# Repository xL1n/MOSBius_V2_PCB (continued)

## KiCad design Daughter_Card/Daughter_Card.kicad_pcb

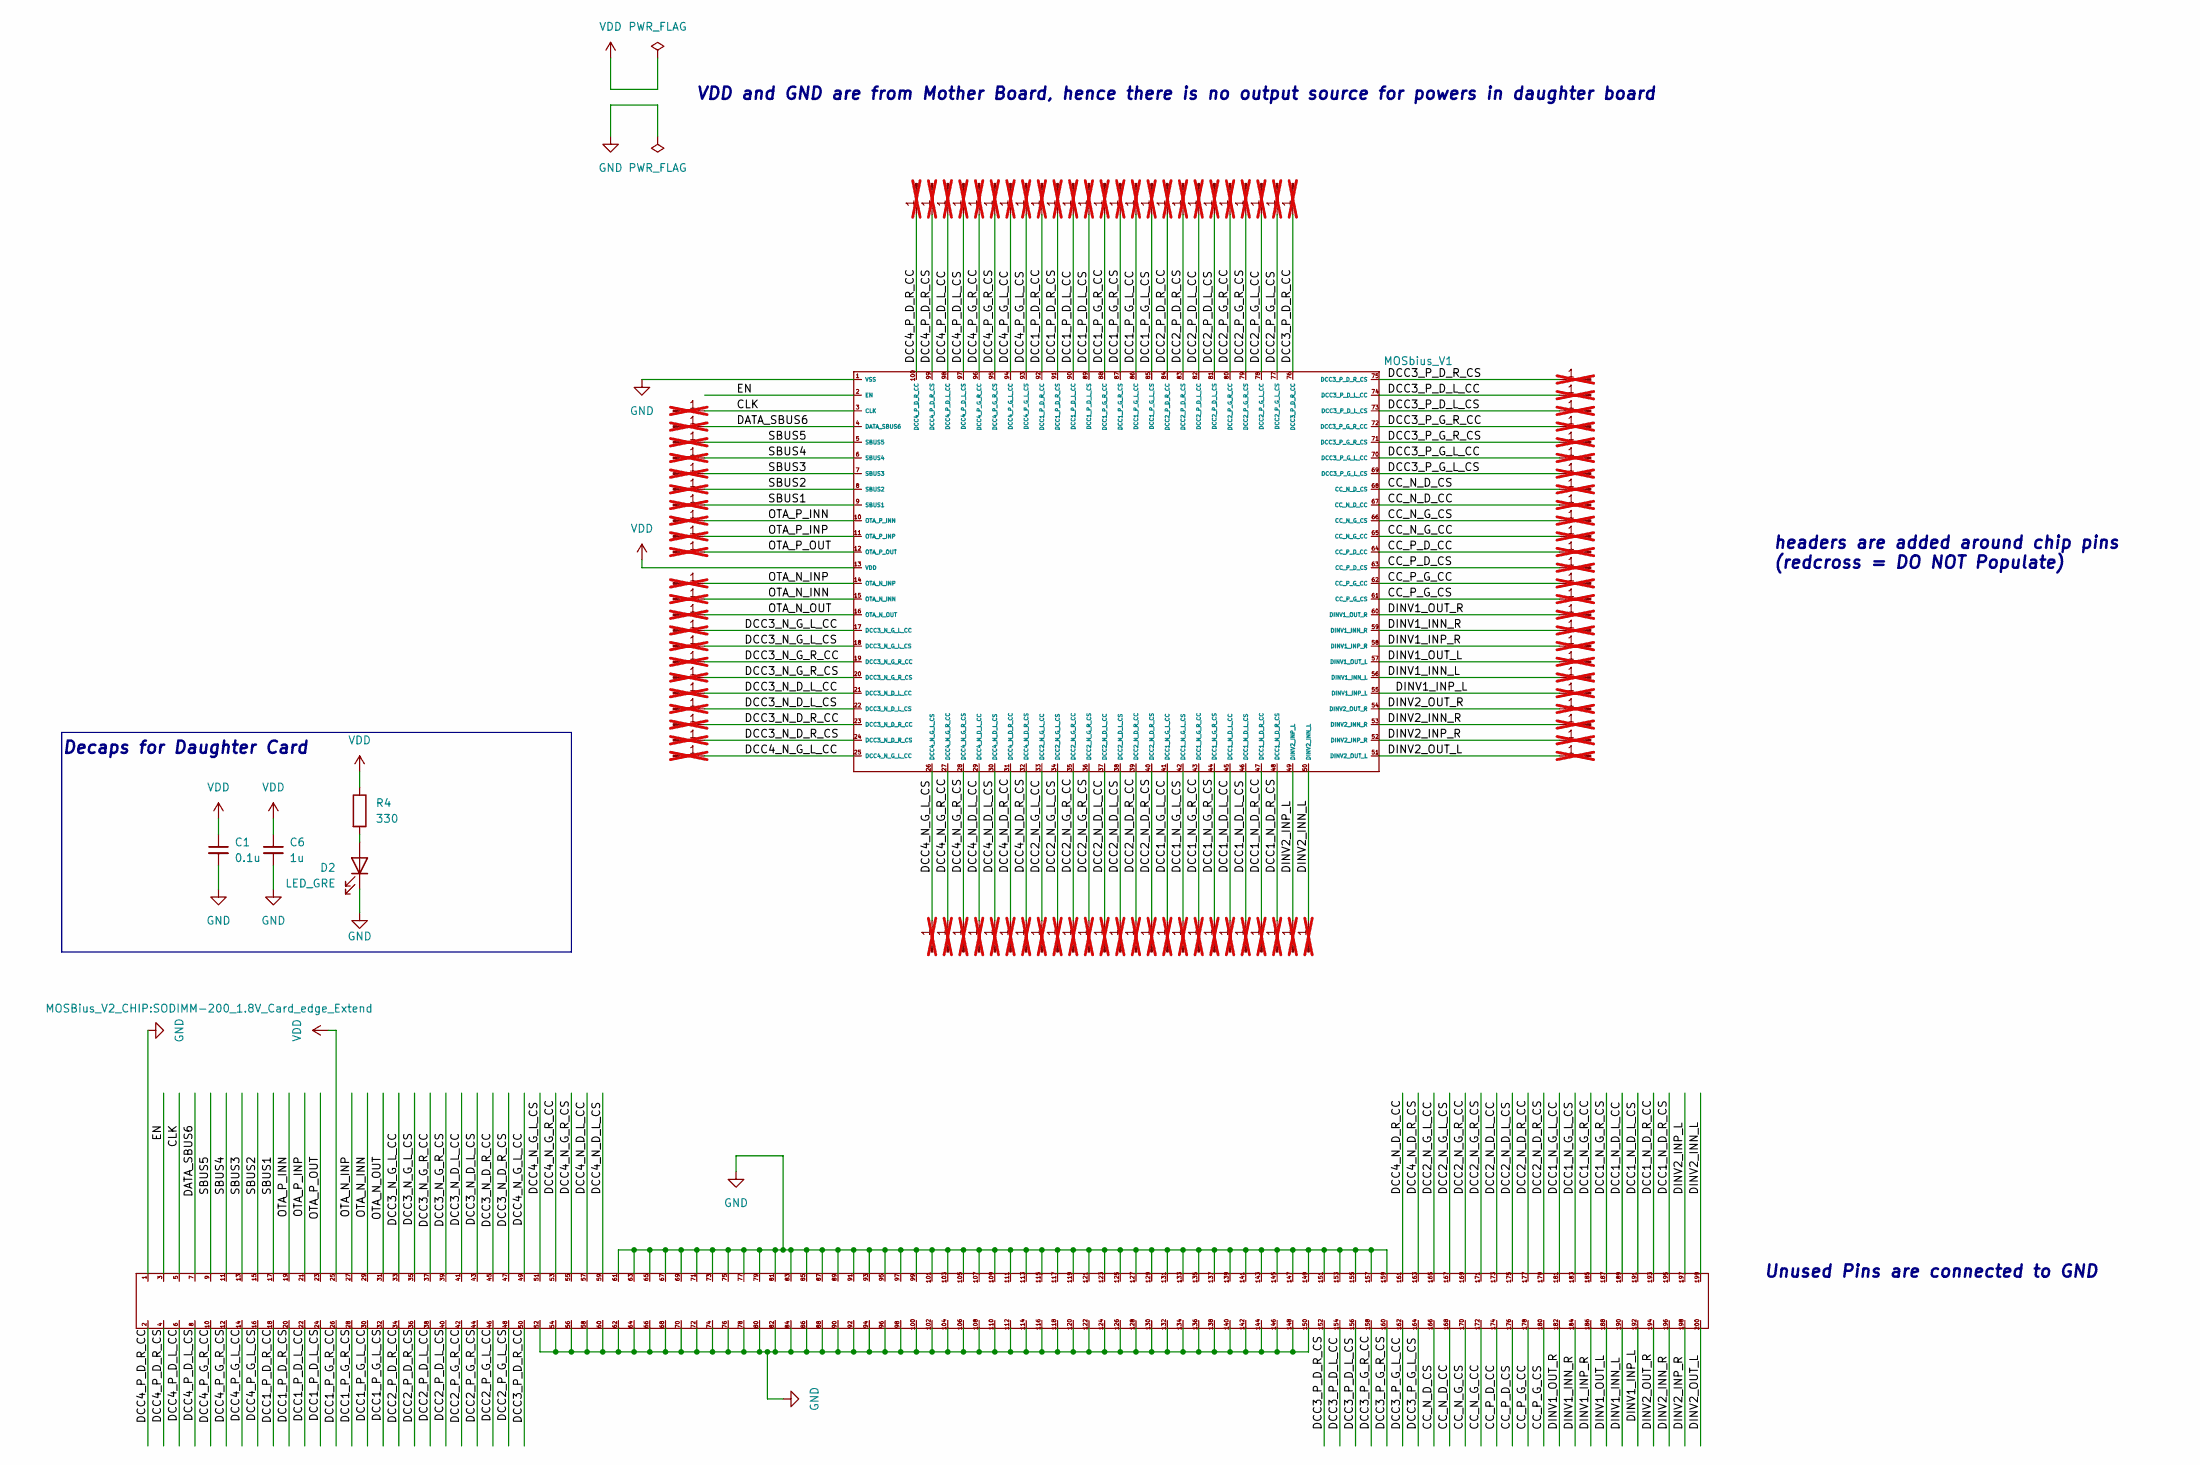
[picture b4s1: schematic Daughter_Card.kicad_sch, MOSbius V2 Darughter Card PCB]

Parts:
C1: 0.1u; C_0603_1608Metric
C6: 1u; C_0603_1608Metric
D2: LED_GRE; LED_150120RS75000_WRE
Daughter_Card_PIN1: SODIMM-200_1.8V_Card_edge_Extend
MOSbius_V1: MOSbius_V2; ArtInChip_QFN-100-1EP_12x12mm_P0.4mm_EP7.4x7.4mm
P3, P4, P5, P6, P7, P8, P9, P10, P11, P12, P14, P15, P16, P17, P18, P19, P20, P21, P22, P23, P24, P25, P26, P27, P28, P29, P30, P31, P32, P33, P34, P35, P36, P37, P38, P39, P40, P41, P42, P43, P44, P45, P46, P47, P48, P49, P50, P51, P52, P53, P54, P55, P56, P57, P58, P59, P60, P61, P62, P63, P64, P65, P66, P67, P68, P69, P70, P71, P72, P73, P74, P75, P76, P77, P78, P79, P80, P81, P82, P83, P84, P85, P86, P87, P88, P89, P90, P91, P92, P93, P94, P95, P96, P97, P98, P99, P100: Conn_01x01_Pin; PinHeader_1x01_P1.00mm_Vertical; not fitted
R4: 330; R_0603_1608Metric

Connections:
/CC_N_D_CC: Daughter_Card_PIN1.168, MOSbius_V1.67 (CC_N_D_CC), P67.1; also elsewhere on the board
/CC_N_D_CS: Daughter_Card_PIN1.166, MOSbius_V1.68 (CC_N_D_CS), P68.1; also elsewhere on the board
/CC_N_G_CC: Daughter_Card_PIN1.172, MOSbius_V1.65 (CC_N_G_CC), P65.1; also elsewhere on the board
/CC_N_G_CS: Daughter_Card_PIN1.170, MOSbius_V1.66 (CC_N_G_CS), P66.1; also elsewhere on the board
/CC_P_D_CC: Daughter_Card_PIN1.174, MOSbius_V1.64 (CC_P_D_CC), P64.1; also elsewhere on the board
/CC_P_D_CS: Daughter_Card_PIN1.176, MOSbius_V1.63 (CC_P_D_CS), P63.1; also elsewhere on the board
/CC_P_G_CC: Daughter_Card_PIN1.178, MOSbius_V1.62 (CC_P_G_CC), P62.1; also elsewhere on the board
/CC_P_G_CS: Daughter_Card_PIN1.180, MOSbius_V1.61 (CC_P_G_CS), P61.1; also elsewhere on the board
/CLK: Daughter_Card_PIN1.5, MOSbius_V1.3 (CLK), P3.1; also elsewhere on the board
/DATA_SBUS6: Daughter_Card_PIN1.7, MOSbius_V1.4 (DATA_SBUS6), P4.1; also elsewhere on the board
/DCC1_N_D_L_CC: Daughter_Card_PIN1.189, MOSbius_V1.45 (DCC1_N_D_L_CC), P45.1; also elsewhere on the board
/DCC1_N_D_L_CS: Daughter_Card_PIN1.191, MOSbius_V1.46 (DCC1_N_D_L_CS), P46.1; also elsewhere on the board
/DCC1_N_D_R_CC: Daughter_Card_PIN1.193, MOSbius_V1.47 (DCC1_N_D_R_CC), P47.1; also elsewhere on the board
/DCC1_N_D_R_CS: Daughter_Card_PIN1.195, MOSbius_V1.48 (DCC1_N_D_R_CS), P48.1; also elsewhere on the board
/DCC1_N_G_L_CC: Daughter_Card_PIN1.181, MOSbius_V1.41 (DCC1_N_G_L_CC), P41.1; also elsewhere on the board
/DCC1_N_G_L_CS: Daughter_Card_PIN1.183, MOSbius_V1.42 (DCC1_N_G_L_CS), P42.1; also elsewhere on the board
/DCC1_N_G_R_CC: Daughter_Card_PIN1.185, MOSbius_V1.43 (DCC1_N_G_R_CC), P43.1; also elsewhere on the board
/DCC1_N_G_R_CS: Daughter_Card_PIN1.187, MOSbius_V1.44 (DCC1_N_G_R_CS), P44.1; also elsewhere on the board
/DCC1_P_D_L_CC: Daughter_Card_PIN1.22, MOSbius_V1.90 (DCC1_P_D_L_CC), P90.1; also elsewhere on the board
/DCC1_P_D_L_CS: Daughter_Card_PIN1.24, MOSbius_V1.89 (DCC1_P_D_L_CS), P89.1; also elsewhere on the board
/DCC1_P_D_R_CC: Daughter_Card_PIN1.18, MOSbius_V1.92 (DCC1_P_D_R_CC), P92.1; also elsewhere on the board
/DCC1_P_D_R_CS: Daughter_Card_PIN1.20, MOSbius_V1.91 (DCC1_P_D_R_CS), P91.1; also elsewhere on the board
/DCC1_P_G_L_CC: Daughter_Card_PIN1.30, MOSbius_V1.86 (DCC1_P_G_L_CC), P86.1; also elsewhere on the board
/DCC1_P_G_L_CS: Daughter_Card_PIN1.32, MOSbius_V1.85 (DCC1_P_G_L_CS), P85.1; also elsewhere on the board
/DCC1_P_G_R_CC: Daughter_Card_PIN1.26, MOSbius_V1.88 (DCC1_P_G_R_CC), P88.1; also elsewhere on the board
/DCC1_P_G_R_CS: Daughter_Card_PIN1.28, MOSbius_V1.87 (DCC1_P_G_R_CS), P87.1; also elsewhere on the board
/DCC2_N_D_L_CC: Daughter_Card_PIN1.173, MOSbius_V1.37 (DCC2_N_D_L_CC), P37.1; also elsewhere on the board
/DCC2_N_D_L_CS: Daughter_Card_PIN1.175, MOSbius_V1.38 (DCC2_N_D_L_CS), P38.1; also elsewhere on the board
/DCC2_N_D_R_CC: Daughter_Card_PIN1.177, MOSbius_V1.39 (DCC2_N_D_R_CC), P39.1; also elsewhere on the board
/DCC2_N_D_R_CS: Daughter_Card_PIN1.179, MOSbius_V1.40 (DCC2_N_D_R_CS), P40.1; also elsewhere on the board
/DCC2_N_G_L_CC: Daughter_Card_PIN1.165, MOSbius_V1.33 (DCC2_N_G_L_CC), P33.1; also elsewhere on the board
/DCC2_N_G_L_CS: Daughter_Card_PIN1.167, MOSbius_V1.34 (DCC2_N_G_L_CS), P34.1; also elsewhere on the board
/DCC2_N_G_R_CC: Daughter_Card_PIN1.169, MOSbius_V1.35 (DCC2_N_G_R_CC), P35.1; also elsewhere on the board
/DCC2_N_G_R_CS: Daughter_Card_PIN1.171, MOSbius_V1.36 (DCC2_N_G_R_CS), P36.1; also elsewhere on the board
/DCC2_P_D_L_CC: Daughter_Card_PIN1.38, MOSbius_V1.82 (DCC2_P_D_L_CC), P82.1; also elsewhere on the board
/DCC2_P_D_L_CS: Daughter_Card_PIN1.40, MOSbius_V1.81 (DCC2_P_D_L_CS), P81.1; also elsewhere on the board
/DCC2_P_D_R_CC: Daughter_Card_PIN1.34, MOSbius_V1.84 (DCC2_P_D_R_CC), P84.1; also elsewhere on the board
/DCC2_P_D_R_CS: Daughter_Card_PIN1.36, MOSbius_V1.83 (DCC2_P_D_R_CS), P83.1; also elsewhere on the board
/DCC2_P_G_L_CC: Daughter_Card_PIN1.46, MOSbius_V1.78 (DCC2_P_G_L_CC), P78.1; also elsewhere on the board
/DCC2_P_G_L_CS: Daughter_Card_PIN1.48, MOSbius_V1.77 (DCC2_P_G_L_CS), P77.1; also elsewhere on the board
/DCC2_P_G_R_CC: Daughter_Card_PIN1.42, MOSbius_V1.80 (DCC2_P_G_R_CC), P80.1; also elsewhere on the board
/DCC2_P_G_R_CS: Daughter_Card_PIN1.44, MOSbius_V1.79 (DCC2_P_G_R_CS), P79.1; also elsewhere on the board
/DCC3_N_D_L_CC: Daughter_Card_PIN1.41, MOSbius_V1.21 (DCC3_N_D_L_CC), P21.1; also elsewhere on the board
/DCC3_N_D_L_CS: Daughter_Card_PIN1.43, MOSbius_V1.22 (DCC3_N_D_L_CS), P22.1; also elsewhere on the board
/DCC3_N_D_R_CC: Daughter_Card_PIN1.45, MOSbius_V1.23 (DCC3_N_D_R_CC), P23.1; also elsewhere on the board
/DCC3_N_D_R_CS: Daughter_Card_PIN1.47, MOSbius_V1.24 (DCC3_N_D_R_CS), P24.1; also elsewhere on the board
/DCC3_N_G_L_CC: Daughter_Card_PIN1.33, MOSbius_V1.17 (DCC3_N_G_L_CC), P17.1; also elsewhere on the board
/DCC3_N_G_L_CS: Daughter_Card_PIN1.35, MOSbius_V1.18 (DCC3_N_G_L_CS), P18.1; also elsewhere on the board
/DCC3_N_G_R_CC: Daughter_Card_PIN1.37, MOSbius_V1.19 (DCC3_N_G_R_CC), P19.1; also elsewhere on the board
/DCC3_N_G_R_CS: Daughter_Card_PIN1.39, MOSbius_V1.20 (DCC3_N_G_R_CS), P20.1; also elsewhere on the board
/DCC3_P_D_L_CC: Daughter_Card_PIN1.154, MOSbius_V1.74 (DCC3_P_D_L_CC), P74.1; also elsewhere on the board
/DCC3_P_D_L_CS: Daughter_Card_PIN1.156, MOSbius_V1.73 (DCC3_P_D_L_CS), P73.1; also elsewhere on the board
/DCC3_P_D_R_CC: Daughter_Card_PIN1.50, MOSbius_V1.76 (DCC3_P_D_R_CC), P76.1; also elsewhere on the board
/DCC3_P_D_R_CS: Daughter_Card_PIN1.152, MOSbius_V1.75 (DCC3_P_D_R_CS), P75.1; also elsewhere on the board
/DCC3_P_G_L_CC: Daughter_Card_PIN1.162, MOSbius_V1.70 (DCC3_P_G_L_CC), P70.1; also elsewhere on the board
/DCC3_P_G_L_CS: Daughter_Card_PIN1.164, MOSbius_V1.69 (DCC3_P_G_L_CS), P69.1; also elsewhere on the board
/DCC3_P_G_R_CC: Daughter_Card_PIN1.158, MOSbius_V1.72 (DCC3_P_G_R_CC), P72.1; also elsewhere on the board
/DCC3_P_G_R_CS: Daughter_Card_PIN1.160, MOSbius_V1.71 (DCC3_P_G_R_CS), P71.1; also elsewhere on the board
/DCC4_N_D_L_CC: Daughter_Card_PIN1.57, MOSbius_V1.29 (DCC4_N_D_L_CC), P29.1; also elsewhere on the board
/DCC4_N_D_L_CS: Daughter_Card_PIN1.59, MOSbius_V1.30 (DCC4_N_D_L_CS), P30.1; also elsewhere on the board
/DCC4_N_D_R_CC: Daughter_Card_PIN1.161, MOSbius_V1.31 (DCC4_N_D_R_CC), P31.1; also elsewhere on the board
/DCC4_N_D_R_CS: Daughter_Card_PIN1.163, MOSbius_V1.32 (DCC4_N_D_R_CS), P32.1; also elsewhere on the board
/DCC4_N_G_L_CC: Daughter_Card_PIN1.49, MOSbius_V1.25 (DCC4_N_G_L_CC), P25.1; also elsewhere on the board
/DCC4_N_G_L_CS: Daughter_Card_PIN1.51, MOSbius_V1.26 (DCC4_N_G_L_CS), P26.1; also elsewhere on the board
/DCC4_N_G_R_CC: Daughter_Card_PIN1.53, MOSbius_V1.27 (DCC4_N_G_R_CC), P27.1; also elsewhere on the board
/DCC4_N_G_R_CS: Daughter_Card_PIN1.55, MOSbius_V1.28 (DCC4_N_G_R_CS), P28.1; also elsewhere on the board
/DCC4_P_D_L_CC: Daughter_Card_PIN1.6, MOSbius_V1.98 (DCC4_P_D_L_CC), P98.1; also elsewhere on the board
/DCC4_P_D_L_CS: Daughter_Card_PIN1.8, MOSbius_V1.97 (DCC4_P_D_L_CS), P97.1; also elsewhere on the board
/DCC4_P_D_R_CC: Daughter_Card_PIN1.2, MOSbius_V1.100 (DCC4_P_D_R_CC), P100.1; also elsewhere on the board
/DCC4_P_D_R_CS: Daughter_Card_PIN1.4, MOSbius_V1.99 (DCC4_P_D_R_CS), P99.1; also elsewhere on the board
/DCC4_P_G_L_CC: Daughter_Card_PIN1.14, MOSbius_V1.94 (DCC4_P_G_L_CC), P94.1; also elsewhere on the board
/DCC4_P_G_L_CS: Daughter_Card_PIN1.16, MOSbius_V1.93 (DCC4_P_G_L_CS), P93.1; also elsewhere on the board
/DCC4_P_G_R_CC: Daughter_Card_PIN1.10, MOSbius_V1.96 (DCC4_P_G_R_CC), P96.1; also elsewhere on the board
/DCC4_P_G_R_CS: Daughter_Card_PIN1.12, MOSbius_V1.95 (DCC4_P_G_R_CS), P95.1; also elsewhere on the board
/DINV1_INN_L: Daughter_Card_PIN1.190, MOSbius_V1.56 (DINV1_INN_L), P56.1; also elsewhere on the board
/DINV1_INN_R: Daughter_Card_PIN1.184, MOSbius_V1.59 (DINV1_INN_R), P59.1; also elsewhere on the board
/DINV1_INP_L: Daughter_Card_PIN1.192, MOSbius_V1.55 (DINV1_INP_L), P55.1; also elsewhere on the board
/DINV1_INP_R: Daughter_Card_PIN1.186, MOSbius_V1.58 (DINV1_INP_R), P58.1; also elsewhere on the board
/DINV1_OUT_L: Daughter_Card_PIN1.188, MOSbius_V1.57 (DINV1_OUT_L), P57.1; also elsewhere on the board
/DINV1_OUT_R: Daughter_Card_PIN1.182, MOSbius_V1.60 (DINV1_OUT_R), P60.1; also elsewhere on the board
/DINV2_INN_L: Daughter_Card_PIN1.199, MOSbius_V1.50 (DINV2_INN_L), P50.1; also elsewhere on the board
/DINV2_INN_R: Daughter_Card_PIN1.196, MOSbius_V1.53 (DINV2_INN_R), P53.1; also elsewhere on the board
/DINV2_INP_L: Daughter_Card_PIN1.197, MOSbius_V1.49 (DINV2_INP_L), P49.1; also elsewhere on the board
/DINV2_INP_R: Daughter_Card_PIN1.198, MOSbius_V1.52 (DINV2_INP_R), P52.1; also elsewhere on the board
/DINV2_OUT_L: Daughter_Card_PIN1.200, MOSbius_V1.51 (DINV2_OUT_L), P51.1; also elsewhere on the board
/DINV2_OUT_R: Daughter_Card_PIN1.194, MOSbius_V1.54 (DINV2_OUT_R), P54.1; also elsewhere on the board
/EN: Daughter_Card_PIN1.3, MOSbius_V1.2 (EN); also elsewhere on the board
/OTA_N_INN: Daughter_Card_PIN1.29, MOSbius_V1.15 (OTA_N_INN), P15.1; also elsewhere on the board
/OTA_N_INP: Daughter_Card_PIN1.27, MOSbius_V1.14 (OTA_N_INP), P14.1; also elsewhere on the board
/OTA_N_OUT: Daughter_Card_PIN1.31, MOSbius_V1.16 (OTA_N_OUT), P16.1; also elsewhere on the board
/OTA_P_INN: Daughter_Card_PIN1.19, MOSbius_V1.10 (OTA_P_INN), P10.1; also elsewhere on the board
/OTA_P_INP: Daughter_Card_PIN1.21, MOSbius_V1.11 (OTA_P_INP), P11.1; also elsewhere on the board
/OTA_P_OUT: Daughter_Card_PIN1.23, MOSbius_V1.12 (OTA_P_OUT), P12.1; also elsewhere on the board
/SBUS1: Daughter_Card_PIN1.17, MOSbius_V1.9 (SBUS1), P9.1; also elsewhere on the board
/SBUS2: Daughter_Card_PIN1.15, MOSbius_V1.8 (SBUS2), P8.1; also elsewhere on the board
/SBUS3: Daughter_Card_PIN1.13, MOSbius_V1.7 (SBUS3), P7.1; also elsewhere on the board
/SBUS4: Daughter_Card_PIN1.11, MOSbius_V1.6 (SBUS4), P6.1; also elsewhere on the board
/SBUS5: Daughter_Card_PIN1.9, MOSbius_V1.5 (SBUS5), P5.1; also elsewhere on the board
GND: C1.2, C6.2, D2.1 (K), Daughter_Card_PIN1.1, Daughter_Card_PIN1.52, Daughter_Card_PIN1.54, Daughter_Card_PIN1.56, Daughter_Card_PIN1.58, Daughter_Card_PIN1.60, Daughter_Card_PIN1.61, Daughter_Card_PIN1.62, Daughter_Card_PIN1.63, Daughter_Card_PIN1.64, Daughter_Card_PIN1.65, Daughter_Card_PIN1.66, Daughter_Card_PIN1.67, Daughter_Card_PIN1.68, Daughter_Card_PIN1.69, Daughter_Card_PIN1.70, Daughter_Card_PIN1.71, Daughter_Card_PIN1.72, Daughter_Card_PIN1.73, Daughter_Card_PIN1.74, Daughter_Card_PIN1.75, Daughter_Card_PIN1.76, Daughter_Card_PIN1.77, Daughter_Card_PIN1.78, Daughter_Card_PIN1.79, Daughter_Card_PIN1.80, Daughter_Card_PIN1.81, Daughter_Card_PIN1.82, Daughter_Card_PIN1.83, Daughter_Card_PIN1.84, Daughter_Card_PIN1.85, Daughter_Card_PIN1.86, Daughter_Card_PIN1.87, Daughter_Card_PIN1.88, Daughter_Card_PIN1.89, Daughter_Card_PIN1.90, Daughter_Card_PIN1.91, Daughter_Card_PIN1.92, Daughter_Card_PIN1.93, Daughter_Card_PIN1.94, Daughter_Card_PIN1.95, Daughter_Card_PIN1.96, Daughter_Card_PIN1.97, Daughter_Card_PIN1.98, Daughter_Card_PIN1.99, Daughter_Card_PIN1.100, Daughter_Card_PIN1.101, Daughter_Card_PIN1.102, Daughter_Card_PIN1.103, Daughter_Card_PIN1.104, Daughter_Card_PIN1.105, Daughter_Card_PIN1.106, Daughter_Card_PIN1.107, Daughter_Card_PIN1.108, Daughter_Card_PIN1.109, Daughter_Card_PIN1.110, Daughter_Card_PIN1.111, Daughter_Card_PIN1.112, Daughter_Card_PIN1.113, Daughter_Card_PIN1.114, Daughter_Card_PIN1.115, Daughter_Card_PIN1.116, Daughter_Card_PIN1.117, Daughter_Card_PIN1.118, Daughter_Card_PIN1.119, Daughter_Card_PIN1.120, Daughter_Card_PIN1.121, Daughter_Card_PIN1.122, Daughter_Card_PIN1.123, Daughter_Card_PIN1.124, Daughter_Card_PIN1.125, Daughter_Card_PIN1.126, Daughter_Card_PIN1.127, Daughter_Card_PIN1.128, Daughter_Card_PIN1.129, Daughter_Card_PIN1.130, Daughter_Card_PIN1.131, Daughter_Card_PIN1.132, Daughter_Card_PIN1.133, Daughter_Card_PIN1.134, Daughter_Card_PIN1.135, Daughter_Card_PIN1.136, Daughter_Card_PIN1.137, Daughter_Card_PIN1.138, Daughter_Card_PIN1.139, Daughter_Card_PIN1.140, Daughter_Card_PIN1.141, Daughter_Card_PIN1.142, Daughter_Card_PIN1.143, Daughter_Card_PIN1.144, Daughter_Card_PIN1.145, Daughter_Card_PIN1.146, Daughter_Card_PIN1.147, Daughter_Card_PIN1.148, Daughter_Card_PIN1.149, Daughter_Card_PIN1.150, Daughter_Card_PIN1.151, Daughter_Card_PIN1.153, Daughter_Card_PIN1.155, Daughter_Card_PIN1.157, Daughter_Card_PIN1.159, MOSbius_V1.1 (VSS); also elsewhere on the board
unnamed: D2.2 (A), R4.2
VDD: C1.1, C6.1, Daughter_Card_PIN1.25, MOSbius_V1.13 (VDD), R4.1; also elsewhere on the board

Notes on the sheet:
headers are added around chip pins (redcross = DO NOT Populate)
Decaps for Daughter Card
Unused Pins are connected to GND
VDD and GND are from Mother Board, hence there is no output source for powers in daughter board

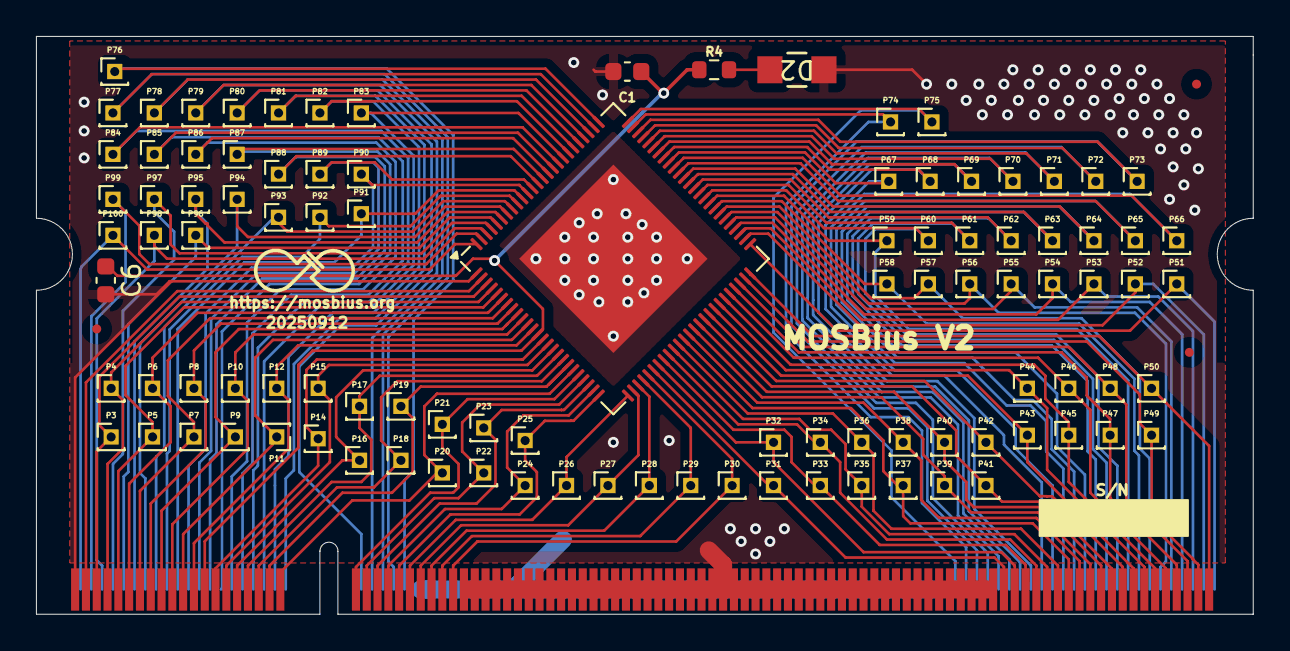
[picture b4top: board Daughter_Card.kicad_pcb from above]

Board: 2 copper layers, 67.6 x 32.1 mm, 103 parts (0 on the bottom side), 101 nets.

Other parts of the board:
MOSbius_V2: MOSbius_V2; ArtInChip_QFN-100-1EP_12x12mm_P0.4mm_EP7.4x7.4mm

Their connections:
/CC_N_D_CC: MOSbius_V2.67 (CC_N_D_CC); also elsewhere on the board
/CC_N_D_CS: MOSbius_V2.68 (CC_N_D_CS); also elsewhere on the board
/CC_N_G_CC: MOSbius_V2.65 (CC_N_G_CC); also elsewhere on the board
/CC_N_G_CS: MOSbius_V2.66 (CC_N_G_CS); also elsewhere on the board
/CC_P_D_CC: MOSbius_V2.64 (CC_P_D_CC); also elsewhere on the board
/CC_P_D_CS: MOSbius_V2.63 (CC_P_D_CS); also elsewhere on the board
/CC_P_G_CC: MOSbius_V2.62 (CC_P_G_CC); also elsewhere on the board
/CC_P_G_CS: MOSbius_V2.61 (CC_P_G_CS); also elsewhere on the board
/CLK: MOSbius_V2.3 (CLK); also elsewhere on the board
/DATA_SBUS6: MOSbius_V2.4 (DATA_SBUS6); also elsewhere on the board
/DCC1_N_D_L_CC: MOSbius_V2.45 (DCC1_N_D_L_CC); also elsewhere on the board
/DCC1_N_D_L_CS: MOSbius_V2.46 (DCC1_N_D_L_CS); also elsewhere on the board
/DCC1_N_D_R_CC: MOSbius_V2.47 (DCC1_N_D_R_CC); also elsewhere on the board
/DCC1_N_D_R_CS: MOSbius_V2.48 (DCC1_N_D_R_CS); also elsewhere on the board
/DCC1_N_G_L_CC: MOSbius_V2.41 (DCC1_N_G_L_CC); also elsewhere on the board
/DCC1_N_G_L_CS: MOSbius_V2.42 (DCC1_N_G_L_CS); also elsewhere on the board
/DCC1_N_G_R_CC: MOSbius_V2.43 (DCC1_N_G_R_CC); also elsewhere on the board
/DCC1_N_G_R_CS: MOSbius_V2.44 (DCC1_N_G_R_CS); also elsewhere on the board
/DCC1_P_D_L_CC: MOSbius_V2.90 (DCC1_P_D_L_CC); also elsewhere on the board
/DCC1_P_D_L_CS: MOSbius_V2.89 (DCC1_P_D_L_CS); also elsewhere on the board
/DCC1_P_D_R_CC: MOSbius_V2.92 (DCC1_P_D_R_CC); also elsewhere on the board
/DCC1_P_D_R_CS: MOSbius_V2.91 (DCC1_P_D_R_CS); also elsewhere on the board
/DCC1_P_G_L_CC: MOSbius_V2.86 (DCC1_P_G_L_CC); also elsewhere on the board
/DCC1_P_G_L_CS: MOSbius_V2.85 (DCC1_P_G_L_CS); also elsewhere on the board
/DCC1_P_G_R_CC: MOSbius_V2.88 (DCC1_P_G_R_CC); also elsewhere on the board
/DCC1_P_G_R_CS: MOSbius_V2.87 (DCC1_P_G_R_CS); also elsewhere on the board
/DCC2_N_D_L_CC: MOSbius_V2.37 (DCC2_N_D_L_CC); also elsewhere on the board
/DCC2_N_D_L_CS: MOSbius_V2.38 (DCC2_N_D_L_CS); also elsewhere on the board
/DCC2_N_D_R_CC: MOSbius_V2.39 (DCC2_N_D_R_CC); also elsewhere on the board
/DCC2_N_D_R_CS: MOSbius_V2.40 (DCC2_N_D_R_CS); also elsewhere on the board
/DCC2_N_G_L_CC: MOSbius_V2.33 (DCC2_N_G_L_CC); also elsewhere on the board
/DCC2_N_G_L_CS: MOSbius_V2.34 (DCC2_N_G_L_CS); also elsewhere on the board
/DCC2_N_G_R_CC: MOSbius_V2.35 (DCC2_N_G_R_CC); also elsewhere on the board
/DCC2_N_G_R_CS: MOSbius_V2.36 (DCC2_N_G_R_CS); also elsewhere on the board
/DCC2_P_D_L_CC: MOSbius_V2.82 (DCC2_P_D_L_CC); also elsewhere on the board
/DCC2_P_D_L_CS: MOSbius_V2.81 (DCC2_P_D_L_CS); also elsewhere on the board
/DCC2_P_D_R_CC: MOSbius_V2.84 (DCC2_P_D_R_CC); also elsewhere on the board
/DCC2_P_D_R_CS: MOSbius_V2.83 (DCC2_P_D_R_CS); also elsewhere on the board
/DCC2_P_G_L_CC: MOSbius_V2.78 (DCC2_P_G_L_CC); also elsewhere on the board
/DCC2_P_G_L_CS: MOSbius_V2.77 (DCC2_P_G_L_CS); also elsewhere on the board
/DCC2_P_G_R_CC: MOSbius_V2.80 (DCC2_P_G_R_CC); also elsewhere on the board
/DCC2_P_G_R_CS: MOSbius_V2.79 (DCC2_P_G_R_CS); also elsewhere on the board
/DCC3_N_D_L_CC: MOSbius_V2.21 (DCC3_N_D_L_CC); also elsewhere on the board
/DCC3_N_D_L_CS: MOSbius_V2.22 (DCC3_N_D_L_CS); also elsewhere on the board
/DCC3_N_D_R_CC: MOSbius_V2.23 (DCC3_N_D_R_CC); also elsewhere on the board
/DCC3_N_D_R_CS: MOSbius_V2.24 (DCC3_N_D_R_CS); also elsewhere on the board
/DCC3_N_G_L_CC: MOSbius_V2.17 (DCC3_N_G_L_CC); also elsewhere on the board
/DCC3_N_G_L_CS: MOSbius_V2.18 (DCC3_N_G_L_CS); also elsewhere on the board
/DCC3_N_G_R_CC: MOSbius_V2.19 (DCC3_N_G_R_CC); also elsewhere on the board
/DCC3_N_G_R_CS: MOSbius_V2.20 (DCC3_N_G_R_CS); also elsewhere on the board
/DCC3_P_D_L_CC: MOSbius_V2.74 (DCC3_P_D_L_CC); also elsewhere on the board
/DCC3_P_D_L_CS: MOSbius_V2.73 (DCC3_P_D_L_CS); also elsewhere on the board
/DCC3_P_D_R_CC: MOSbius_V2.76 (DCC3_P_D_R_CC); also elsewhere on the board
/DCC3_P_D_R_CS: MOSbius_V2.75 (DCC3_P_D_R_CS); also elsewhere on the board
/DCC3_P_G_L_CC: MOSbius_V2.70 (DCC3_P_G_L_CC); also elsewhere on the board
/DCC3_P_G_L_CS: MOSbius_V2.69 (DCC3_P_G_L_CS); also elsewhere on the board
/DCC3_P_G_R_CC: MOSbius_V2.72 (DCC3_P_G_R_CC); also elsewhere on the board
/DCC3_P_G_R_CS: MOSbius_V2.71 (DCC3_P_G_R_CS); also elsewhere on the board
/DCC4_N_D_L_CC: MOSbius_V2.29 (DCC4_N_D_L_CC); also elsewhere on the board
/DCC4_N_D_L_CS: MOSbius_V2.30 (DCC4_N_D_L_CS); also elsewhere on the board
/DCC4_N_D_R_CC: MOSbius_V2.31 (DCC4_N_D_R_CC); also elsewhere on the board
/DCC4_N_D_R_CS: MOSbius_V2.32 (DCC4_N_D_R_CS); also elsewhere on the board
/DCC4_N_G_L_CC: MOSbius_V2.25 (DCC4_N_G_L_CC); also elsewhere on the board
/DCC4_N_G_L_CS: MOSbius_V2.26 (DCC4_N_G_L_CS); also elsewhere on the board
/DCC4_N_G_R_CC: MOSbius_V2.27 (DCC4_N_G_R_CC); also elsewhere on the board
/DCC4_N_G_R_CS: MOSbius_V2.28 (DCC4_N_G_R_CS); also elsewhere on the board
/DCC4_P_D_L_CC: MOSbius_V2.98 (DCC4_P_D_L_CC); also elsewhere on the board
/DCC4_P_D_L_CS: MOSbius_V2.97 (DCC4_P_D_L_CS); also elsewhere on the board
/DCC4_P_D_R_CC: MOSbius_V2.100 (DCC4_P_D_R_CC); also elsewhere on the board
/DCC4_P_D_R_CS: MOSbius_V2.99 (DCC4_P_D_R_CS); also elsewhere on the board
/DCC4_P_G_L_CC: MOSbius_V2.94 (DCC4_P_G_L_CC); also elsewhere on the board
/DCC4_P_G_L_CS: MOSbius_V2.93 (DCC4_P_G_L_CS); also elsewhere on the board
/DCC4_P_G_R_CC: MOSbius_V2.96 (DCC4_P_G_R_CC); also elsewhere on the board
/DCC4_P_G_R_CS: MOSbius_V2.95 (DCC4_P_G_R_CS); also elsewhere on the board
/DINV1_INN_L: MOSbius_V2.56 (DINV1_INN_L); also elsewhere on the board
/DINV1_INN_R: MOSbius_V2.59 (DINV1_INN_R); also elsewhere on the board
/DINV1_INP_L: MOSbius_V2.55 (DINV1_INP_L); also elsewhere on the board
/DINV1_INP_R: MOSbius_V2.58 (DINV1_INP_R); also elsewhere on the board
/DINV1_OUT_L: MOSbius_V2.57 (DINV1_OUT_L); also elsewhere on the board
/DINV1_OUT_R: MOSbius_V2.60 (DINV1_OUT_R); also elsewhere on the board
/DINV2_INN_L: MOSbius_V2.50 (DINV2_INN_L); also elsewhere on the board
/DINV2_INN_R: MOSbius_V2.53 (DINV2_INN_R); also elsewhere on the board
/DINV2_INP_L: MOSbius_V2.49 (DINV2_INP_L); also elsewhere on the board
/DINV2_INP_R: MOSbius_V2.52 (DINV2_INP_R); also elsewhere on the board
/DINV2_OUT_L: MOSbius_V2.51 (DINV2_OUT_L); also elsewhere on the board
/DINV2_OUT_R: MOSbius_V2.54 (DINV2_OUT_R); also elsewhere on the board
/EN: MOSbius_V2.2 (EN); also elsewhere on the board
/OTA_N_INN: MOSbius_V2.15 (OTA_N_INN); also elsewhere on the board
/OTA_N_INP: MOSbius_V2.14 (OTA_N_INP); also elsewhere on the board
/OTA_N_OUT: MOSbius_V2.16 (OTA_N_OUT); also elsewhere on the board
/OTA_P_INN: MOSbius_V2.10 (OTA_P_INN); also elsewhere on the board
/OTA_P_INP: MOSbius_V2.11 (OTA_P_INP); also elsewhere on the board
/OTA_P_OUT: MOSbius_V2.12 (OTA_P_OUT); also elsewhere on the board
/SBUS1: MOSbius_V2.9 (SBUS1); also elsewhere on the board
/SBUS2: MOSbius_V2.8 (SBUS2); also elsewhere on the board
/SBUS3: MOSbius_V2.7 (SBUS3); also elsewhere on the board
/SBUS4: MOSbius_V2.6 (SBUS4); also elsewhere on the board
/SBUS5: MOSbius_V2.5 (SBUS5); also elsewhere on the board
GND: MOSbius_V2.1 (VSS); also elsewhere on the board
VDD: MOSbius_V2.13 (VDD); also elsewhere on the board

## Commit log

2025-09-01 Mother Board and Daughter Board upload on 1/9/2025
2025-09-14 update in 0912
2025-09-19 0919
2025-09-19 add DigiKey cart
2025-10-16 1016
2026-03-12 0311_2026 XP update - mainly in RPI board
